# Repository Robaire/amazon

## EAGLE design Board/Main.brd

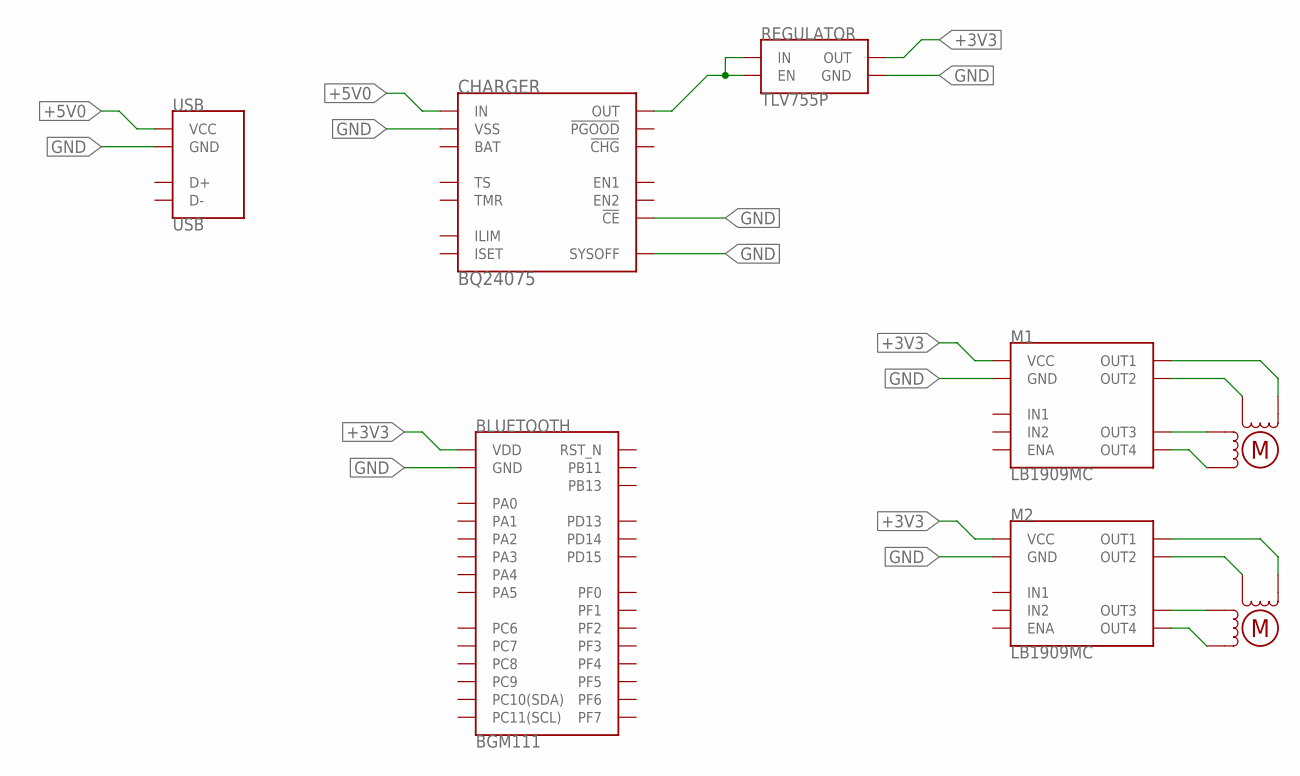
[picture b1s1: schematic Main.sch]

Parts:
BLUETOOTH: BGM111
CHARGER: BQ24075; VQFN-16
M1, M2: LB1909MC; SOIC-10
REGULATOR: TLV755P; SOT-23-5
U$3, U$4: MOTOR
USB: USB

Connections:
+3V3: BLUETOOTH.VDD, M1.1 (VCC), M2.1 (VCC), REGULATOR.5 (OUT)
+5V0: CHARGER.13 (IN), USB.1 (VCC)
GND: BLUETOOTH.GND@0 (GND), BLUETOOTH.GND@1 (GND), BLUETOOTH.GND@2 (GND), BLUETOOTH.GND@3 (GND), CHARGER.4 (!CE), CHARGER.8 (VSS), CHARGER.15 (SYSOFF), CHARGER.17 (VSS), CHARGER.17@1 (VSS), CHARGER.17@2 (VSS), CHARGER.17@3 (VSS), CHARGER.17@4 (VSS), M1.6 (GND), M2.6 (GND), REGULATOR.2 (GND), USB.5 (GND), USB.GND@0 (GND), USB.GND@1 (GND), USB.GND@2 (GND), USB.GND@3 (GND)
unnamed: CHARGER.10 (OUT), CHARGER.11 (OUT), REGULATOR.1 (IN), REGULATOR.3 (EN)
unnamed: M1.7 (OUT4), U$4.B2
unnamed: M2.7 (OUT4), U$3.B2
unnamed: M2.8 (OUT3), U$3.B1
unnamed: M1.8 (OUT3), U$4.B1
unnamed: M1.9 (OUT2), U$4.A1
unnamed: M1.10 (OUT1), U$4.A2
unnamed: M2.9 (OUT2), U$3.A1
unnamed: M2.10 (OUT1), U$3.A2

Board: 2 copper layers, 13 parts (5 on the bottom side), 12 nets, no tracks yet.

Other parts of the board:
LI-PO: 500mAh; BATTERY
U$1, U$2, U$5, U$6: #4_SCREW

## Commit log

2018-11-01 Ignore file backup versions
2018-11-01 Create main files
2018-11-01 Change name
2018-11-01 Add battery managment
2018-11-01 Create library for hardware components
2018-11-01 Remove datasheets
2018-11-01 Bluetooth Module Datasheet
2018-11-01 Battery Managment Datasheet
2018-11-02 Add motor driver
2018-11-02 Regulator
2018-11-02 Motor Driver
2018-11-02 Create CAD model
2018-11-02 Micro USB Connector
2018-11-02 Add USB connector
2018-11-02 Add battery outline
2018-11-02 Add USB and update Motor
2018-11-02 Add Mouser links
2018-11-03 Update Model
